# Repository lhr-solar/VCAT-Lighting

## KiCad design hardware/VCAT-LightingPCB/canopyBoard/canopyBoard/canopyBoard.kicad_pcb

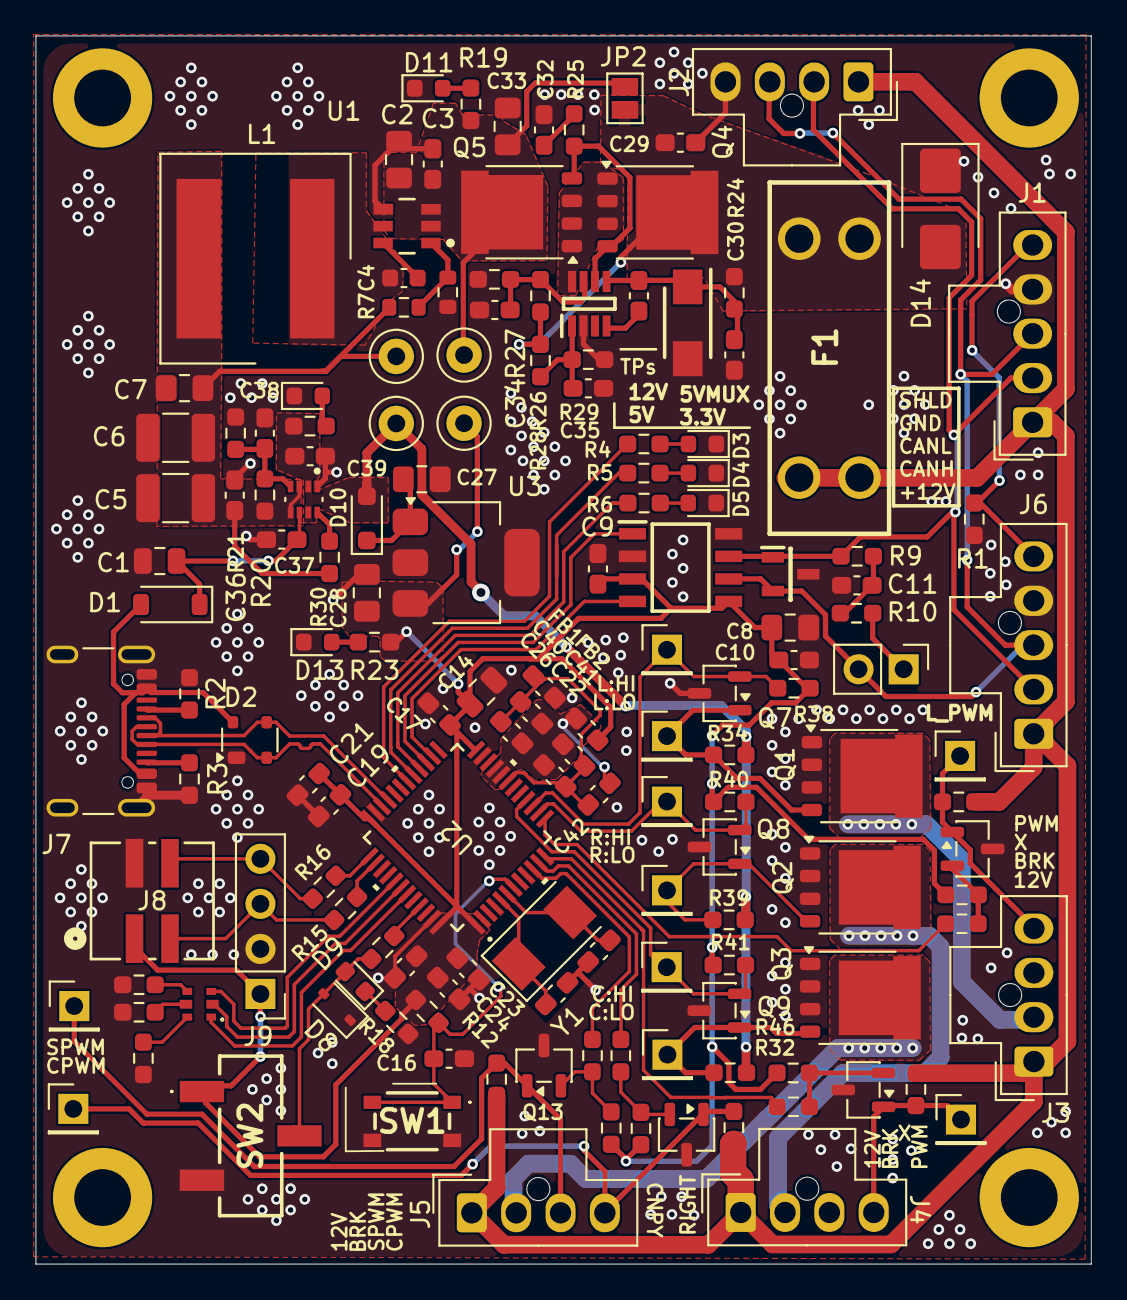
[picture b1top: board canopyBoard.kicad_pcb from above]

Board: 2 copper layers, 59.5 x 69.2 mm, 156 parts (0 on the bottom side), 81 nets.

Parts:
C1: 10u; C_0805_2012Metric
C2: 4.7u; C_0805_2012Metric_Pad1.18x1.45mm_HandSolder
C3: 100n; C_0603_1608Metric_Pad1.08x0.95mm_HandSolder
C4: 100n; C_0603_1608Metric
C5, C6: 22u; C_1210_3225Metric_Pad1.33x2.70mm_HandSolder
C7: 3.3u; C_0805_2012Metric_Pad1.18x1.45mm_HandSolder
C8, C27, C28, C33: 10u; C_0805_2012Metric_Pad1.18x1.45mm_HandSolder
C9, C10, C11, C29, C34, C35: 0.1u; C_0603_1608Metric_Pad1.08x0.95mm_HandSolder
C12, C13: 26p; C_0603_1608Metric_Pad1.08x0.95mm_HandSolder
C14: 10uF; C_0805_2012Metric
C16, C17, C19, C21, C22, C23, C24, C25, C26, C36, C37, C38, C39: 0.1uF; C_0603_1608Metric_Pad1.08x0.95mm_HandSolder
C30: 1u; C_0603_1608Metric_Pad1.08x0.95mm_HandSolder
C31: 220n; C_0603_1608Metric_Pad1.08x0.95mm_HandSolder
C32: 10n; C_0603_1608Metric_Pad1.08x0.95mm_HandSolder
C40, C41: 1uF; C_0603_1608Metric_Pad1.08x0.95mm_HandSolder
C42: 100nF; C_0603_1608Metric_Pad1.08x0.95mm_HandSolder
D1: D_Schottky; D_SOD-123
D2: SP0503BAHT; SOT-143
D3, D4, D5, D9, D11, D12, D13: LED; LED_0603_1608Metric
D6: CDSOT23-T24CAN
D7: RGB_LED
D8: TVS; D_SOD-323
D10: SBA130CH-AU_R1_000A1; D_SOD-323_HandSoldering
D14: SMBJ15CA; D_SMB
D15: SMAF4758A; SODFL5026X125N
F1: 1A; Fuse-3557-2
FB1, FB2: FerriteBead; C_0603_1608Metric_Pad1.08x0.95mm_HandSolder
H1, H2, H3, H4: MountingHole_Pad; MountingHole_3.2mm_M3_DIN965_Pad
IC1: TCAN3413DR
IC2: LM74502DDFR
J1, J6: CAN_NANO_01x05; Molex_Nano-Fit_105309-xx05_1x05_P2.50mm_Vertical
J2: DEBUG_CAN; Molex_Nano-Fit_105309-xx04_1x04_P2.50mm_Vertical
J3, J4, J5: Conn_02x02_Counter_Clockwise; Molex_Nano-Fit_105309-xx04_1x04_P2.50mm_Vertical
J7: USB_C_Receptacle_USB2.0_16P; USB_C_Receptacle_GCT_USB4105-xx-A_16P_TopMnt_Horizontal
J8: SWD_Header; SWD_Conn
J9: SWD; PinHeader_1x04_P2.54mm_Vertical
JP1: TRM; PinHeader_1x02_P2.54mm_Vertical
JP2: SolderJumper_2_Open; SolderJumper-2_P1.3mm_Open_Pad1.0x1.5mm
L1: 8.2u; 74439369082
Q1, Q2, Q3, Q4, Q5: PSMN012-100YS; LFPAK56
Q7, Q8, Q9, Q10, Q11, Q12, Q13: NMOS; SOT-23-3
R1: 0; R_0603_1608Metric_Pad0.98x0.95mm_HandSolder
R2, R3: 5.1k; R_0603_1608Metric_Pad0.98x0.95mm_HandSolder
R4, R5, R6, R11, R13, R14, R18, R19, R22, R23: 1k; R_0603_1608Metric_Pad0.98x0.95mm_HandSolder
R7: 100k; R_0603_1608Metric
R8: 19.1k; R_0603_1608Metric
R9, R10: 60; R_0603_1608Metric_Pad0.98x0.95mm_HandSolder
R12, R17, R24, R30, R34, R35, R36, R38, R39, R40, R41, R42, R43, R44, R45, R46, R47, R48: 10k; R_0603_1608Metric_Pad0.98x0.95mm_HandSolder
R15, R16: 22; R_0603_1608Metric_Pad0.98x0.95mm_HandSolder
R20: 16k; R_0603_1608Metric_Pad0.98x0.95mm_HandSolder
R21: 4.7K; R_0603_1608Metric_Pad0.98x0.95mm_HandSolder
R25: 33; R_0603_1608Metric_Pad0.98x0.95mm_HandSolder
R26, R28: 100k; R_0603_1608Metric_Pad0.98x0.95mm_HandSolder
R27: 7.32k; R_0603_1608Metric_Pad0.98x0.95mm_HandSolder
R29: 15.8k; R_0603_1608Metric_Pad0.98x0.95mm_HandSolder
R31, R32, R33, R37: 470; R_0603_1608Metric_Pad0.98x0.95mm_HandSolder
SW1: Reset; TL3365AF180QG
SW2: SW_SPDT; BootSW
TP1: TP_12V; TestPoint_Loop_D1.80mm_Drill1.0mm_Beaded
TP2: TP_5V_VIN1; TestPoint_Loop_D1.80mm_Drill1.0mm_Beaded
TP3: TP_5V_MUX; TestPoint_Loop_D1.80mm_Drill1.0mm_Beaded
TP4: LHI_FET; PinHeader_1x01_P2.54mm_Vertical
TP5: RHI_FET; PinHeader_1x01_P2.54mm_Vertical
TP6: CHI_FET; PinHeader_1x01_P2.54mm_Vertical
TP7: LLO_FET; PinHeader_1x01_P2.54mm_Vertical
TP8: RLO_FET; PinHeader_1x01_P2.54mm_Vertical
TP9: CLO_FET; PinHeader_1x01_P2.54mm_Vertical
TP10: TP_3.3V1; TestPoint_Loop_D1.80mm_Drill1.0mm_Beaded
TP11: L_PWM; PinHeader_1x01_P2.54mm_Vertical
TP12: R_PWM; PinHeader_1x01_P2.54mm_Vertical
TP13: C_PWM; PinHeader_1x01_P2.54mm_Vertical
TP14: S_PWM; PinHeader_1x01_P2.54mm_Vertical
U1: LMR51635XDDCR; DDC0006A-MFG
U2: STM32G473CETx; 48PinMCU
U3: MCP1826S; SOT-223-3_TabPin2
U4: TPS2117DRLR
Y1: Crystal; Crystal_SMD_Abracon_ABM3-2Pin_5.0x3.2mm

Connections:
+3.3V: C8.1, C9.1, C10.1, C14.1, C17.1, C19.1, C21.1, C23.1, C24.1, C25.1, C28.2, FB2.1, IC1.3 (VCC), IC1.5 (SHDNV_IO), J8.1, J9.1, R12.2, R23.1, R38.1, R40.1, R41.1, R45.1, R46.1, R47.1, R48.1, SW2.1 (A), TP10.1 (1_1), U2.1 (VBAT), U2.24 (VDD), U2.36 (VDD), U2.48 (VDD), U3.3 (VO)
+5V: C39.1, D10.2 (A), R22.1, R34.2, R36.2, R39.2, TP3.1 (1_1), U4.2 (VOUT), U4.7 (VOUT__1)
+5V_USB: C1.2, C37.1, D1.1 (K), U4.6 (VIN2)
+12V: F1.2, J1.1 (12V), J2.1 (12V), J3.1, J4.1, J5.1, J6.1 (12V), R35.2, R42.2, R43.2, R44.2
+12V_PP: C2.1, C3.1, C33.1, JP2.2 (B), Q5.5, R19.1, TP1.1 (1_1), U1.2 (EN), U1.3 (VIN)
/<NO NET>: J1.5 (SHIELD), J6.5 (SHIELD), R1.2
/CAN_H: D6.1 (CAN_H), IC1.7 (CANH), J1.2 (CAN_H), J2.2 (CAN_H), J6.2 (CAN_H), R9.1
/CAN_L: D6.2 (CAN_L), IC1.6 (CANL), J1.3 (CAN_L), J2.3 (CAN_L), J6.3 (CAN_L), JP1.2 (B)
/CAN_Transceiver/CAN_RX: IC1.4 (RXD), U2.26 (PB12)
/CAN_Transceiver/CAN_TX: IC1.1 (TXD), U2.27 (PB13)
/CPY_BRK: J5.2, Q3.5
/CPY_PWM_OUT: J5.4, Q12.1 (D), R43.1, TP13.1 (1_1)
/Fet Logic/CPY_PWM: Q12.2 (G), R33.2, R47.2
/Fet Logic/CPY_PWRFET: Q9.2 (G), R41.2, TP9.1 (1_1), U2.16 (PB0)
/Fet Logic/L_PWM: Q10.2 (G), R31.2, R45.2
/Fet Logic/L_PWRFET: Q7.2 (G), R38.2, TP7.1 (1_1), U2.15 (PA7)
/Fet Logic/R_PWM: Q11.2 (G), R32.2, R46.2
/Fet Logic/R_PWRFET: Q8.2 (G), R40.2, TP8.1 (1_1), U2.14 (PA6)
/Fet Logic/STRB_PWM: Q13.2 (G), R37.2, R48.2
/L_BRK: J3.2, Q1.5
/L_PWM_OUT: J3.4, Q10.1 (D), R35.1, TP11.1 (1_1)
/MCU/48PinMCU4/BOOT0: R17.1, U2.45 (PB8-BOOT0)
/MCU/48PinMCU4/Blue: D7.5, U2.41 (PB4)
/MCU/48PinMCU4/Green: D7.1, U2.43 (PB6)
/MCU/48PinMCU4/NRST: C16.1, R12.1, SW1.1, U2.7 (PG10-NRST)
/MCU/48PinMCU4/PA8: R4.1, U2.30 (PA8)
/MCU/48PinMCU4/PB14: R6.1, U2.28 (PB14)
/MCU/48PinMCU4/PB15: R5.1, U2.29 (PB15)
/MCU/48PinMCU4/Red: D7.3, U2.42 (PB5)
/MCU/48PinMCU4/SWCLK: R15.1, U2.38 (PA14)
/MCU/48PinMCU4/SWDIO: R16.1, U2.37 (PA13)
/MCU/PWMCPY: R33.1, U2.11 (PA3)
/MCU/PWML: R31.1, U2.13 (PA5)
/MCU/PWMR: R32.1, U2.12 (PA4)
/MCU/PWMSTRB: R37.1, U2.10 (PA2-GPIO_GREEN)
/MCU/USB-C_Connector/CC1: J7.A5 (CC1), R2.2
/MCU/USB-C_Connector/CC2: J7.B5 (CC2), R3.2
/MCU/USB-C_Connector/VBUS_IN: D1.2 (A), D2.4 (K), J7.A4 (VBUS), J7.A9 (VBUS), J7.B4 (VBUS), J7.B9 (VBUS)
/MCU/USB_D+: D2.2 (K), J7.A6 (D+), J7.B6 (D+), U2.34 (PA12)
/MCU/USB_D-: D2.3 (K), J7.A7 (D-), J7.B7 (D-), U2.33 (PA11)
/Power/12VBuck1/CB: C4.1, U1.6 (CB)
/Power/12VBuck1/FB: R7.2, R8.1, U1.1 (FB)
/Power/12VBuck1/SW: C4.2, L1.1, U1.5 (SW)
/Power/12VBuck1/V_out_5V: C5.1, C6.1, C7.1, C36.1, L1.2, R7.1, R20.1, R30.1, TP2.1 (1_1), U4.3 (VIN1), U4.5 (MODE)
/Power/PP1/EN/UVLO: C35.1, IC2.1 (EN/UVLO), R28.2, R29.2
/Power/PP1/OV: C34.1, IC2.7 (OV), R26.2, R27.1
/Power/PP1/Vin: C29.1, D14.2 (A2), F1.1, JP2.1 (A), Q4.5, R24.2, R26.1, R28.1
/Power/PP1/gate: IC2.6 (GATE), Q4.4, Q5.4, R25.2
/Power/PP1/source: IC2.8 (SRC), Q4.1, Q4.2, Q4.3, Q5.1, Q5.2, Q5.3
/Power/Power_Mux1/PR1: C38.1, R20.2, R21.1, U4.4 (PR1)
/R_BRK: J4.2, Q2.5
/R_PWM_OUT: J4.4, Q11.1 (D), R42.1, TP12.1 (1_1)
/STRB_PWM_OUT: J5.3, Q13.1 (D), R44.1, TP14.1 (1_1)
GND: C1.1, C2.2, C3.2, C5.2, C6.2, C7.2, C8.2, C9.2, C10.2, C11.1, C12.1, C13.2, C14.2, C16.2, C17.2, C19.2, C21.2, C23.2, C24.2, C25.2, C27.1, C28.1, C29.2, C30.1, C32.2, C33.2, C34.2, C35.2, C36.2, C37.2, C38.2, C39.2, D2.1 (A), D3.1 (K), D4.1 (K), D5.1 (K), D6.3 (GND), D8.1 (A1), D11.1 (K), D12.1 (K), D13.1 (K), D14.1 (A1), D15.2 (A), FB1.2, IC1.2 (GND), IC1.8 (STB), IC2.2 (GND), J1.4 (GND), J2.4 (GND), J6.4 (GND), J7.A1 (GND), J7.A12 (GND), J7.B1 (GND), J7.B12 (GND), J7.S1 (SHIELD), J7.S2 (Shield), J7.S3 (Shield), J7.S4 (Shield), J8.2, J9.2, Q1.1, Q1.2, Q1.3, Q2.1, Q2.2, Q2.3, Q3.1, Q3.2, Q3.3, Q7.3 (S), Q8.3 (S), Q9.3 (S), Q10.3 (S), Q11.3 (S), Q12.3 (S), Q13.3 (S), R1.1, R2.1, R3.1, R8.2, R11.2, R13.2, R14.2, R18.2, R21.2, R27.2, R29.1, SW1.2, SW2.3 (C), U1.4 (GND), U2.23 (VSS), U2.35 (VSS), U2.47 (VSS), U3.2 (GND), U4.1 (GND)
GNDA: C22.2, C26.2, C40.2, C41.2, C42.2, FB1.1, U2.19 (VSSA)
unnamed: C11.2, R9.2, R10.1
unnamed: C32.1, R25.1
unnamed: D3.2 (A), R4.2
unnamed: D4.2 (A), R5.2
unnamed: D5.2 (A), R6.2
unnamed: D7.2, R11.1
unnamed: D7.4, R13.1
unnamed: D7.6, R14.1
unnamed: D8.2 (A2), D9.2 (A), R17.2, SW2.2 (B)
unnamed: D9.1 (K), R18.1
unnamed: C27.2, D10.1 (K), U3.1 (VI)
unnamed: D11.2 (A), R19.2
unnamed: D12.2 (A), R22.2
unnamed: D13.2 (A), R23.2
unnamed: C30.2, C31.1, D15.1 (K), IC2.5 (VS), R24.1
unnamed: C31.2, IC2.4 (VCAP)
unnamed: J8.3, J9.3, R15.2
unnamed: J8.4, J9.4, R16.2
unnamed: JP1.1 (A), R10.2
unnamed: Q1.4, Q7.1 (D), R34.1, TP4.1 (1_1)
unnamed: Q2.4, Q8.1 (D), R39.1, TP5.1 (1_1)
unnamed: Q3.4, Q9.1 (D), R36.1, TP6.1 (1_1)
unnamed: C12.2, U2.5 (PF0-OSC_IN), Y1.1
unnamed: C13.1, U2.6 (PF1-OSC_OUT), Y1.2
unnamed: R30.2, U4.8 (ST)
VDDA: C22.1, C26.1, C40.1, C41.1, C42.1, FB2.2, U2.20 (VREF+), U2.21 (VDDA)

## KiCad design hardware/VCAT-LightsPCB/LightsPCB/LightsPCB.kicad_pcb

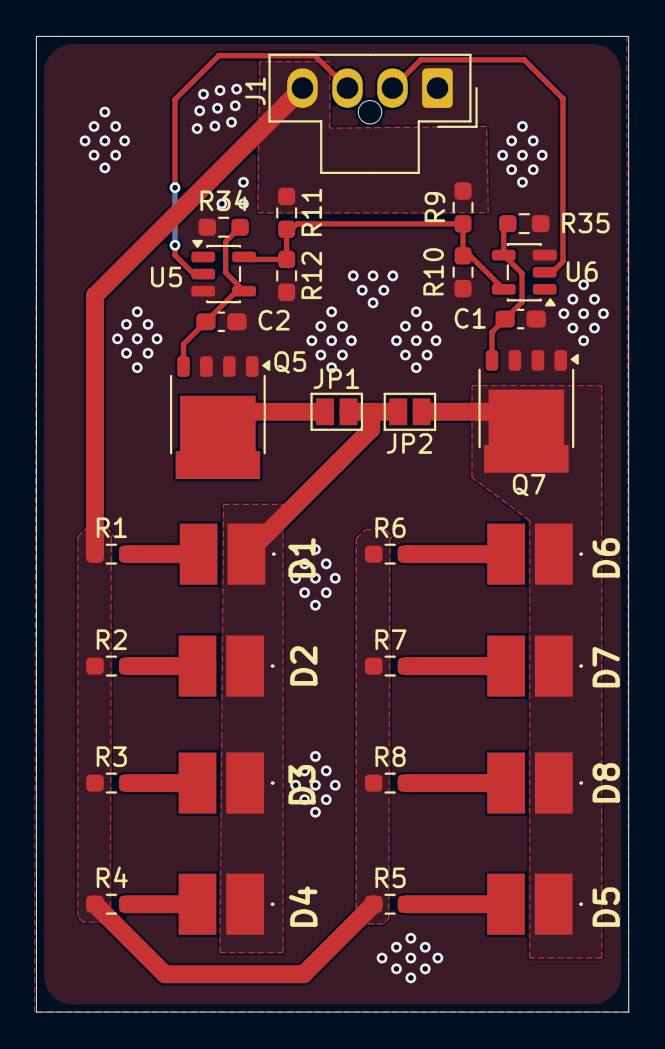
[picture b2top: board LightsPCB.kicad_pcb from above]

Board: 2 copper layers, 32.9 x 54.2 mm, 31 parts (0 on the bottom side), 18 nets.

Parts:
C1, C2: 1n; C_0603_1608Metric_Pad1.08x0.95mm_HandSolder
D1, D2, D3, D4, D5, D6, D7, D8: LED; ABEZD13RA3
J1: Conn_01x04; Molex_Nano-Fit_105309-xx04_1x04_P2.50mm_Vertical
JP1, JP2: SolderJumper_2_Open; SolderJumper-2_P1.3mm_Open_Pad1.0x1.5mm
Q5, Q7: PSMN012-100YS; LFPAK56
R1, R2, R3, R4, R5, R6, R7, R8: 0; R_0603_1608Metric_Pad0.98x0.95mm_HandSolder
R9, R11: 1k; R_0603_1608Metric_Pad0.98x0.95mm_HandSolder
R10, R12: 680; R_0603_1608Metric_Pad0.98x0.95mm_HandSolder
R34, R35: 10k; R_0603_1608Metric_Pad0.98x0.95mm_HandSolder
U5, U6: 74LVC1G17; SOT-23-5

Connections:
+12V: J1.4, R1.1, R2.1, R3.1, R4.1, R5.1, R6.1, R7.1, R8.1, R9.1, R11.1
/BRK_GND: C1.1, C2.1, J1.1, Q5.1, Q5.2, Q5.3, Q7.1, Q7.2, Q7.3, R10.2, R12.2, R34.1, R35.1, U5.3 (GND), U6.3 (GND)
/Logic/5V: R9.2, R10.1, R11.2, R12.1, U5.5 (VCC), U6.5 (VCC)
/PWM1: J1.3, U5.2
/PWM2: J1.2, U6.2
unnamed: C1.2, Q7.4, R35.2, U6.4
unnamed: C2.2, Q5.4, R34.2, U5.4
unnamed: D1.2 (A), R1.2
unnamed: D1.1 (K), D2.1 (K), D3.1 (K), D4.1 (K), JP1.2 (B), JP2.2 (B)
unnamed: D2.2 (A), R2.2
unnamed: D3.2 (A), R3.2
unnamed: D4.2 (A), R4.2
unnamed: D5.2 (A), R5.2
unnamed: D5.1 (K), D6.1 (K), D7.1 (K), D8.1 (K), JP2.1 (A), Q7.5
unnamed: D6.2 (A), R6.2
unnamed: D7.2 (A), R7.2
unnamed: D8.2 (A), R8.2
unnamed: JP1.1 (A), Q5.5
